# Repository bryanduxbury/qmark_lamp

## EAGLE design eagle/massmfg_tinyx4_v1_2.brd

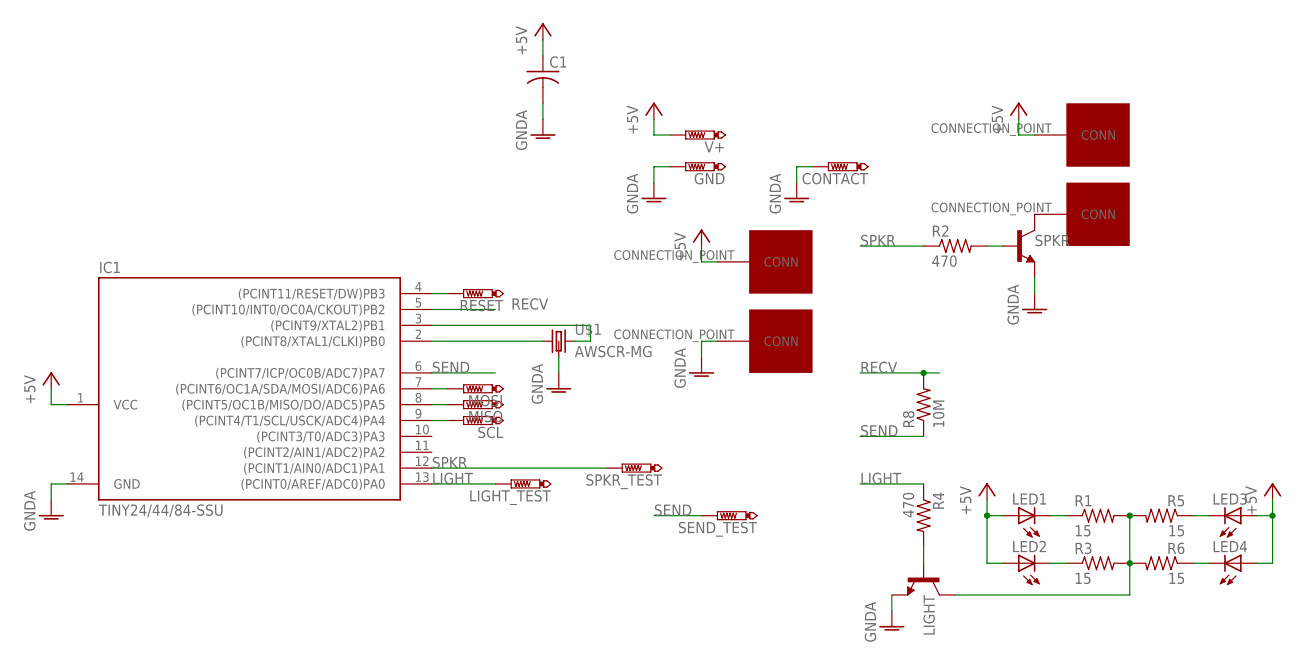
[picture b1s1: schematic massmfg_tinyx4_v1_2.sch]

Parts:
C1: C-USC0603; C0603
CONTACT: PTR1; P1-06
GND: PTR1; P1-06
IC1: TINY24/44/84-SSU; SOIC14
LED1, LED2, LED3, LED4: LEDOPTEK-DURIS5; OPTEK-DURIS5
LIGHT: SOT23-BEC
LIGHT_TEST: PTR1; P1-06
MISO: PTR1; P1-06
MOSI: PTR1; P1-06
R1, R3, R5, R6: 15; M1206
R2, R4: 470; R0805
R8: 10M; M1206
RESET: PTR1; P1-06
SCL: PTR1; P1-06
SEND_TEST: PTR1; P1-06
SPEAKER_PLUS: CONNECTION_POINT; 10X3_CONNECTION_POINT
SPKR: SOT23-BEC
SPKR_MINUS: CONNECTION_POINT; 10X3_CONNECTION_POINT
SPKR_TEST: PTR1; P1-06
U$1: AWSCR-MG
U$3, U$5: CONNECTION_POINT; 10X3_CONNECTION_POINT
V+: PTR1; P1-06

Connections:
+5V: C1.1, IC1.1 (VCC), LED1.ANODE (A), LED2.ANODE (A), LED3.ANODE (A), LED4.ANODE (A), SPEAKER_PLUS.CONNECTION_POINT, U$3.CONNECTION_POINT, V+.TP
GNDA: C1.2, CONTACT.TP, GND.TP, IC1.14 (GND), LIGHT.E, SPKR.E, U$1.GND (3), U$5.CONNECTION_POINT
LIGHT: IC1.13 ((PCINT0/AREF/ADC0)PA0), LIGHT_TEST.TP, R4.1
unnamed: LIGHT.B, R4.2
unnamed: IC1.2 ((PCINT8/XTAL1/CLKI)PB0), U$1.IN (1)
unnamed: LED2.CATHODE (C), R3.1
unnamed: IC1.3 ((PCINT9/XTAL2)PB1), U$1.OUT (2)
unnamed: LED1.CATHODE (C), R1.1
unnamed: R2.2, SPKR.B
unnamed: LED3.CATHODE (C), R5.1
unnamed: LED4.CATHODE (C), R6.1
unnamed: SPKR.C, SPKR_MINUS.CONNECTION_POINT
unnamed: IC1.4 ((PCINT11/RESET/DW)PB3), RESET.TP
unnamed: IC1.7 ((PCINT6/OC1A/SDA/MOSI/ADC6)PA6), MOSI.TP
unnamed: IC1.8 ((PCINT5/OC1B/MISO/DO/ADC5)PA5), MISO.TP
unnamed: IC1.9 ((PCINT4/T1/SCL/USCK/ADC4)PA4), SCL.TP
unnamed: LIGHT.C, R1.2, R3.2, R5.2, R6.2
RECV: IC1.5 ((PCINT10/INT0/OC0A/CKOUT)PB2), R8.2
SEND: IC1.6 ((PCINT7/ICP/OC0B/ADC7)PA7), R8.1, SEND_TEST.TP
SPKR: IC1.12 ((PCINT1/AIN0/ADC1)PA1), R2.1, SPKR_TEST.TP

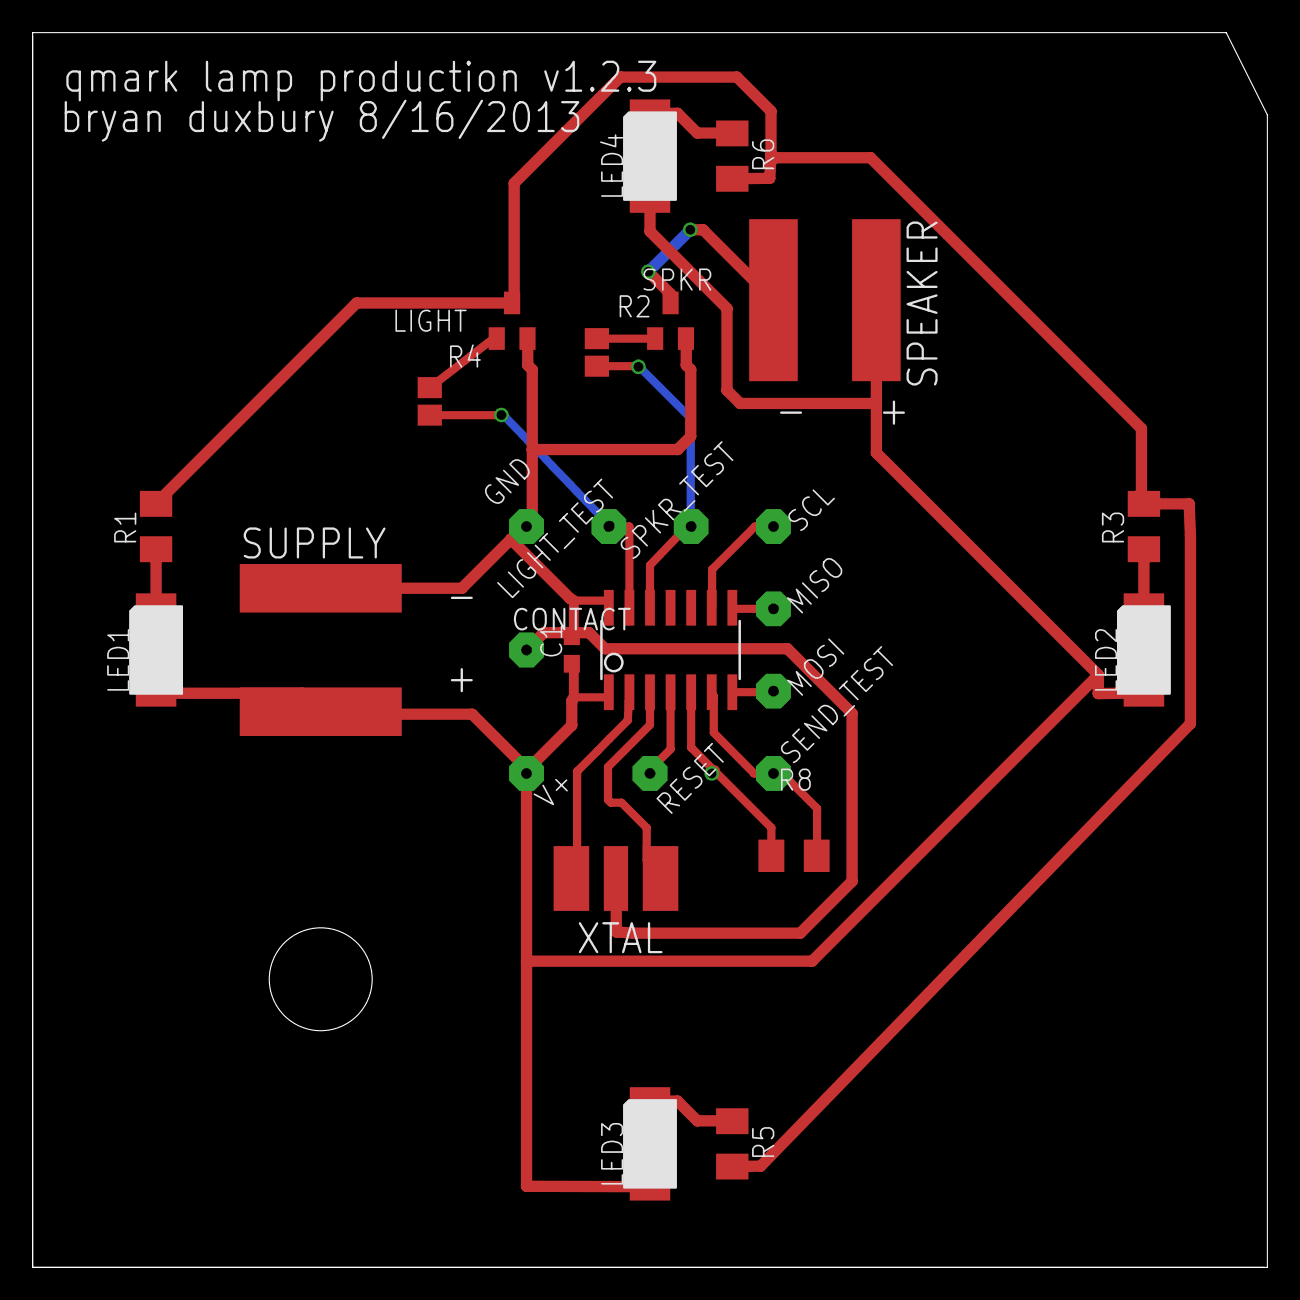
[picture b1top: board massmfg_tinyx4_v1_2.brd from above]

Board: 2 copper layers, 76.2 x 76.2 mm, 30 parts (0 on the bottom side), 20 nets.

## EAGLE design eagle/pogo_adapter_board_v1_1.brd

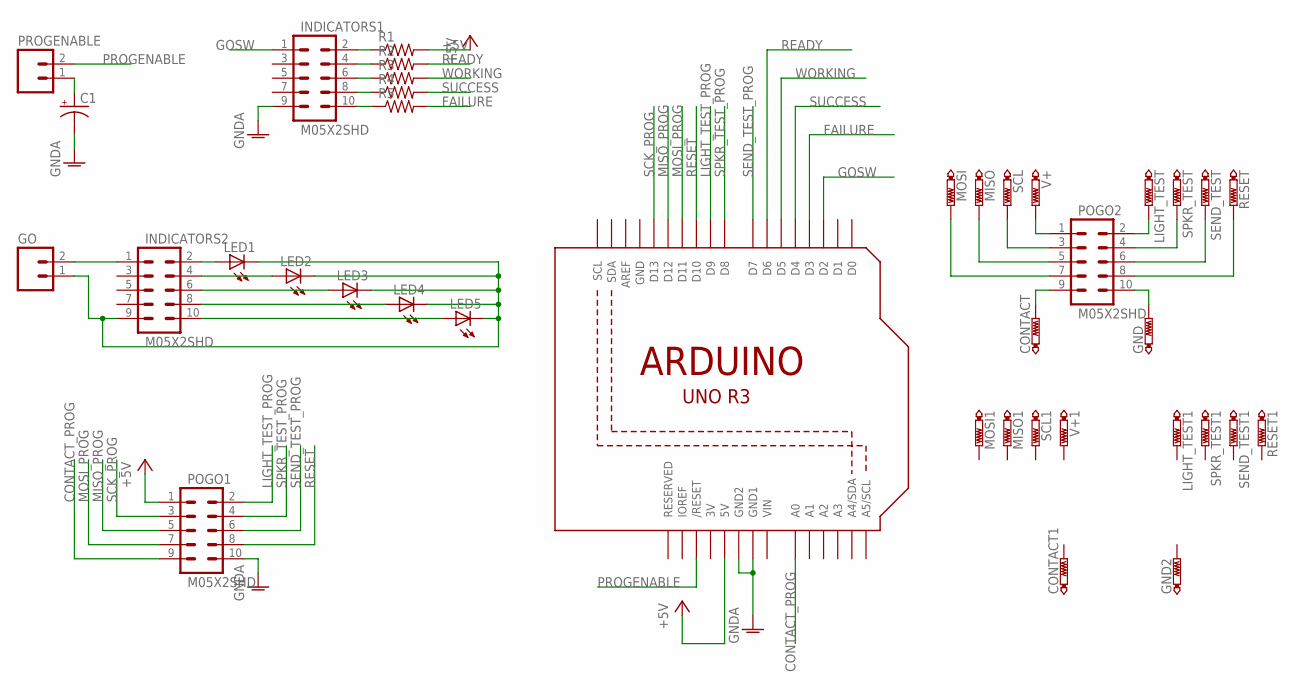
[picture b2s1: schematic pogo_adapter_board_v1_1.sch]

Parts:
C1: CAP_POLPTH2; CPOL-RADIAL-10UF-25V
CONTACT, CONTACT1: PTR1PAD1-13; P1-13
GND, GND2: PTR1PAD1-13; P1-13
GO: M02-JST-2-PTH-NO_SILK; JST-2-PTH-NS
INDICATORS1, INDICATORS2: M05X2SHD; 2X5-SHROUDED
LED1, LED2, LED3, LED4, LED5: LED10MM
LIGHT_TEST, LIGHT_TEST1: PTR1PAD1-13; P1-13
MISO, MISO1: PTR1PAD1-13; P1-13
MOSI, MOSI1: PTR1PAD1-13; P1-13
POGO1, POGO2: M05X2SHD; 2X5-SHROUDED
PROGENABLE: M02-JST-2-PTH-NO_SILK; JST-2-PTH-NS
R1, R2, R3, R4, R5: R-US_0204/7; 0204/7
RESET, RESET1: PTR1PAD1-13; P1-13
SCL, SCL1: PTR1PAD1-13; P1-13
SEND_TEST, SEND_TEST1: PTR1PAD1-13; P1-13
SPKR_TEST, SPKR_TEST1: PTR1PAD1-13; P1-13
U1: ARDUINOR3; ARDUINOR3-MINSHIELD
V+, V+1: PTR1PAD1-13; P1-13

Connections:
3V: U1.3V
+5V: POGO1.1, R1.2, U1.5V
CONTACT_PROG: POGO1.9, U1.A0
FAILURE: R5.2, U1.D3
GND: U1.GND
GNDA: C1.2 (-), INDICATORS1.9, POGO1.10, U1.GND1, U1.GND2
GOSW: INDICATORS1.1, U1.D2
LIGHT_TEST_PROG: POGO1.2, U1.D9
MISO_PROG: POGO1.5, U1.D12
MOSI_PROG: POGO1.7, U1.D11
unnamed: LIGHT_TEST.TP, POGO2.2
unnamed: POGO2.4, SPKR_TEST.TP
unnamed: POGO2.6, SEND_TEST.TP
unnamed: POGO2.8, RESET.TP
unnamed: GND.TP, POGO2.10
unnamed: GO.2, INDICATORS2.1
unnamed: CONTACT.TP, POGO2.9
unnamed: POGO2.3, SCL.TP
unnamed: MISO.TP, POGO2.5
unnamed: MOSI.TP, POGO2.7
unnamed: POGO2.1, V+.TP
unnamed: C1.1 (+), PROGENABLE.1
unnamed: INDICATORS2.2, LED1.A
unnamed: INDICATORS2.4, LED2.A
unnamed: INDICATORS2.6, LED3.A
unnamed: INDICATORS2.8, LED4.A
unnamed: INDICATORS2.10, LED5.A
unnamed: INDICATORS1.2, R1.1
unnamed: INDICATORS1.4, R2.1
unnamed: INDICATORS1.6, R3.1
unnamed: INDICATORS1.8, R4.1
unnamed: INDICATORS1.10, R5.1
unnamed: GO.1, INDICATORS2.9, LED1.K (C), LED2.K (C), LED3.K (C), LED4.K (C), LED5.K (C)
PROGENABLE: PROGENABLE.2, U1.RESET (/RESET)
READY: R2.2, U1.D6
RESET: POGO1.8, U1.D10
SCK_PROG: POGO1.3, U1.D13
SEND_TEST_PROG: POGO1.6, U1.D7
SPKR_TEST_PROG: POGO1.4, U1.D8
SUCCESS: R4.2, U1.D4
VIN: U1.VIN
WORKING: R3.2, U1.D5

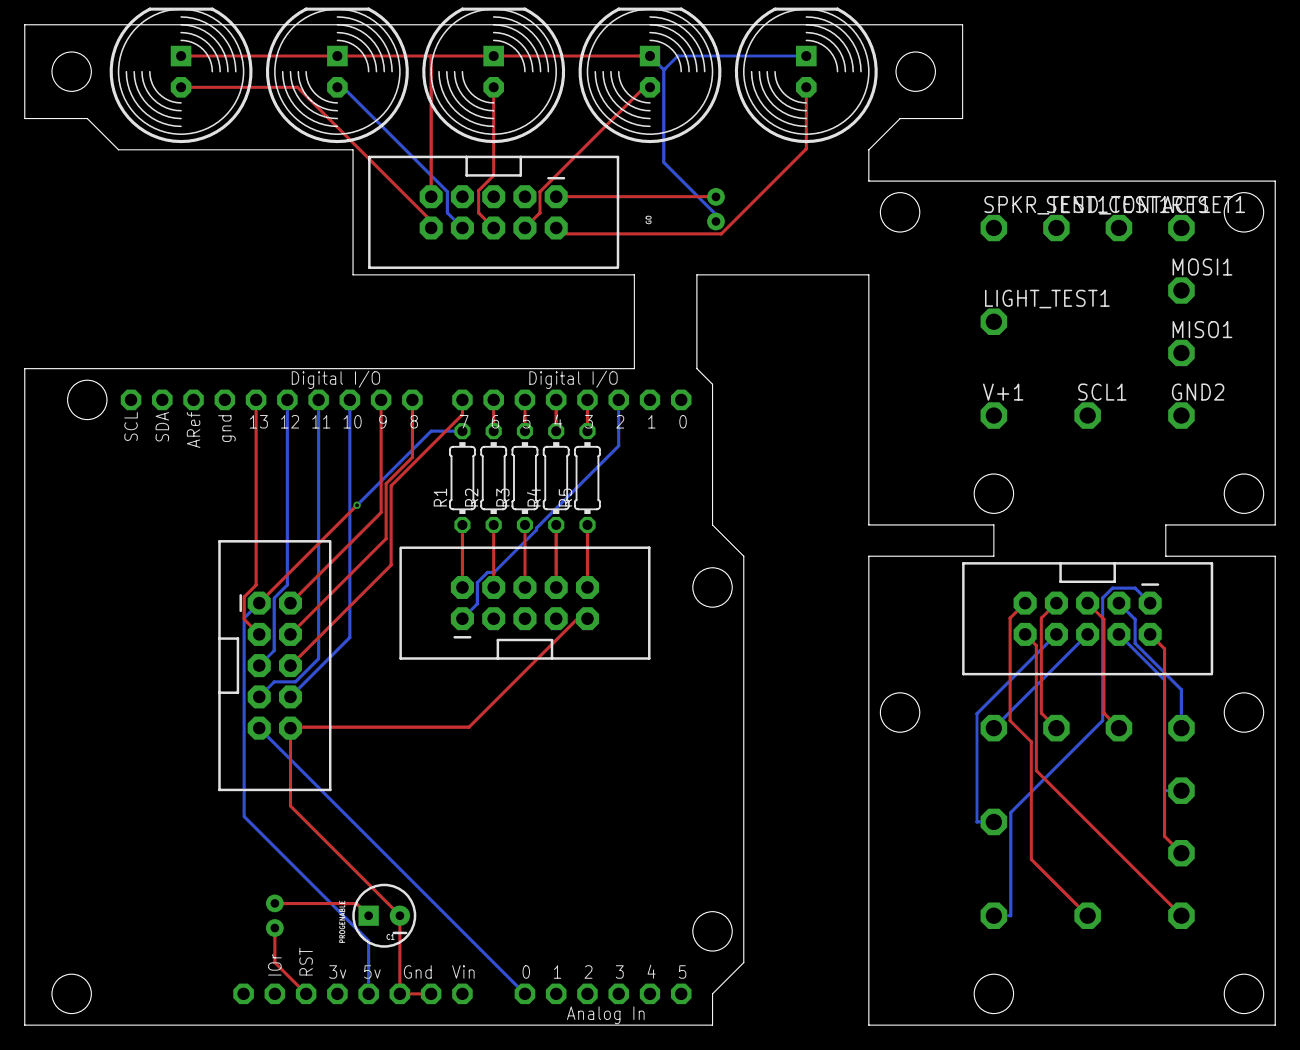
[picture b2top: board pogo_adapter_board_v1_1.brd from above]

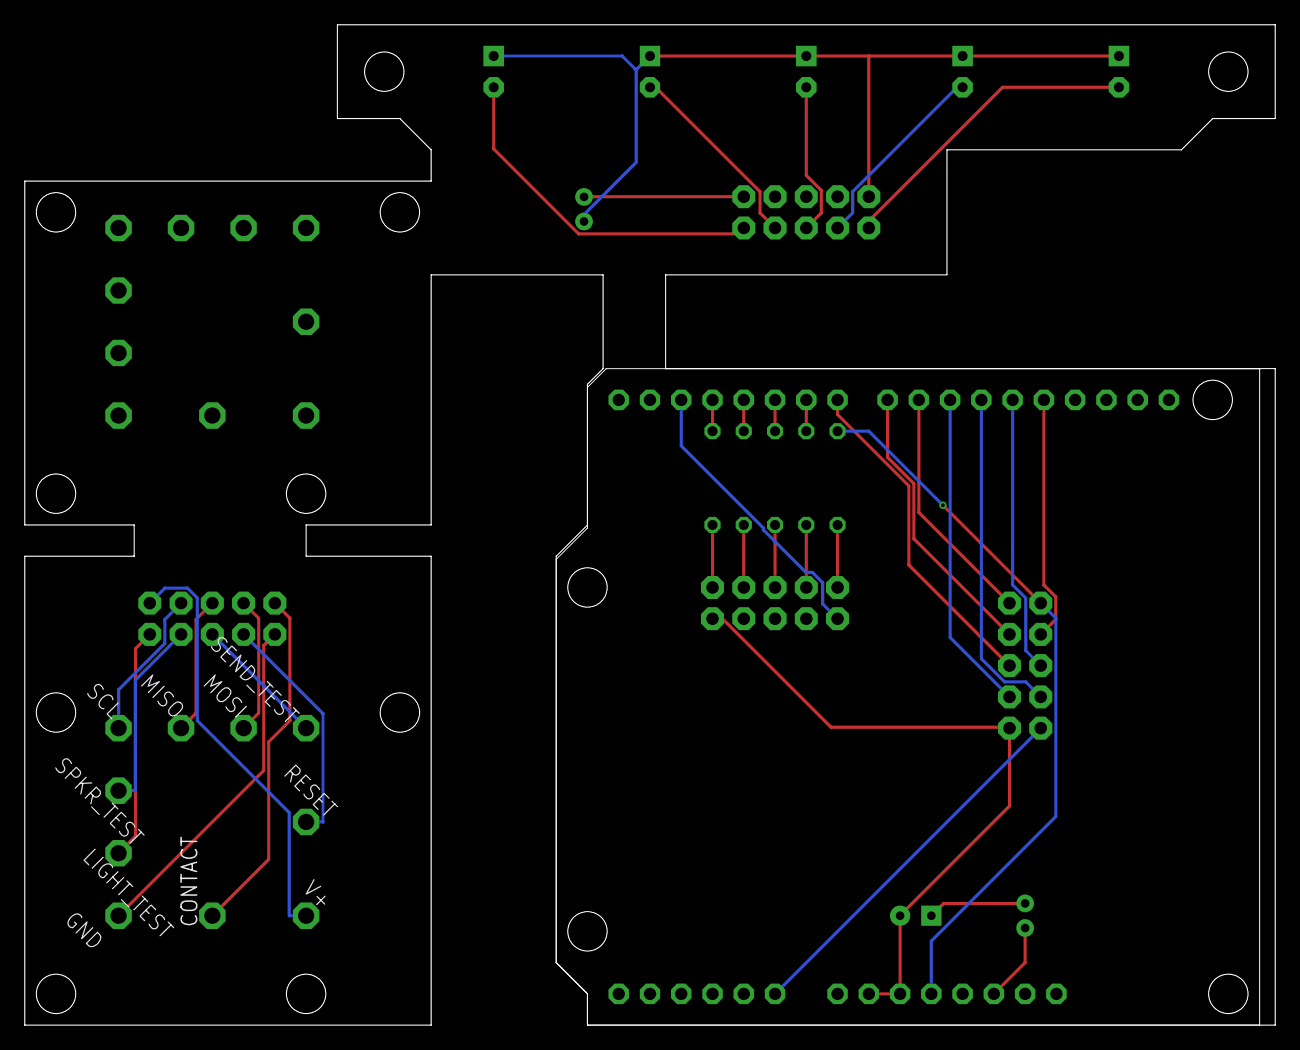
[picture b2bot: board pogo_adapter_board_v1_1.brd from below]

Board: 2 copper layers, 101.6 x 81.3 mm, 38 parts (10 on the bottom side), 39 nets.

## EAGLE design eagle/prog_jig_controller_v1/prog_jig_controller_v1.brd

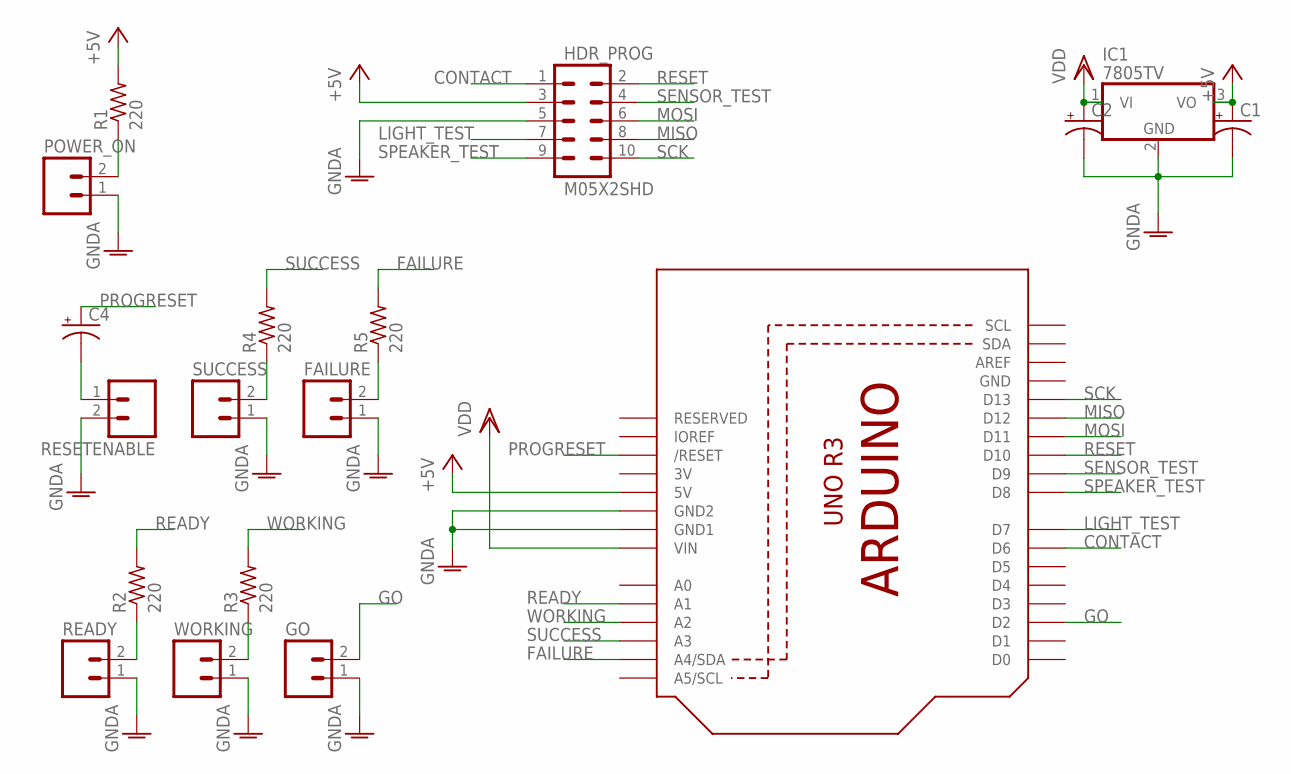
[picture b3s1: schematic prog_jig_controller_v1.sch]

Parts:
C1, C2, C4: CAP_POLPTH2; CPOL-RADIAL-10UF-25V
FAILURE: M02JST-PTH-2; JST-2-PTH
GO: M02JST-PTH-2; JST-2-PTH
HDR_PROG: M05X2SHD; 2X5-SHROUDED
IC1: 7805TV; TO220V
POWER_ON: M02JST-PTH-2; JST-2-PTH
R1, R2, R3, R4, R5: 220; 0204/7
READY: M02JST-PTH-2; JST-2-PTH
RESETENABLE: M02JST-PTH-2; JST-2-PTH
SUCCESS: M02JST-PTH-2; JST-2-PTH
U1: ARDUINOR3-DIMENSION; ARDUINOR3
WORKING: M02JST-PTH-2; JST-2-PTH

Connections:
3V: U1.3V
+5V: C1.1 (+), HDR_PROG.3, IC1.3 (VO), R1.2, U1.5V
CONTACT: HDR_PROG.1, U1.D6
FAILURE: R5.2, U1.A4 (A4/SDA)
GND: U1.GND
GNDA: C1.2 (-), C2.2 (-), FAILURE.1, GO.1, HDR_PROG.5, IC1.2 (GND), POWER_ON.1, READY.1, RESETENABLE.2, SUCCESS.1, U1.GND1, U1.GND2, WORKING.1
GO: GO.2, U1.D2
LIGHT_TEST: HDR_PROG.7, U1.D7
MISO: HDR_PROG.8, U1.D12
MOSI: HDR_PROG.6, U1.D11
unnamed: C4.2 (-), RESETENABLE.1
unnamed: POWER_ON.2, R1.1
unnamed: R4.1, SUCCESS.2
unnamed: R3.1, WORKING.2
unnamed: R2.1, READY.2
unnamed: FAILURE.2, R5.1
PROGRESET: C4.1 (+), U1.RESET (/RESET)
READY: R2.2, U1.A1
RESET: HDR_PROG.2, U1.D10
SCK: HDR_PROG.10, U1.D13
SENSOR_TEST: HDR_PROG.4, U1.D9
SPEAKER_TEST: HDR_PROG.9, U1.D8
SUCCESS: R4.2, U1.A3
VDD: C2.1 (+), IC1.1 (VI), U1.VIN
WORKING: R3.2, U1.A2

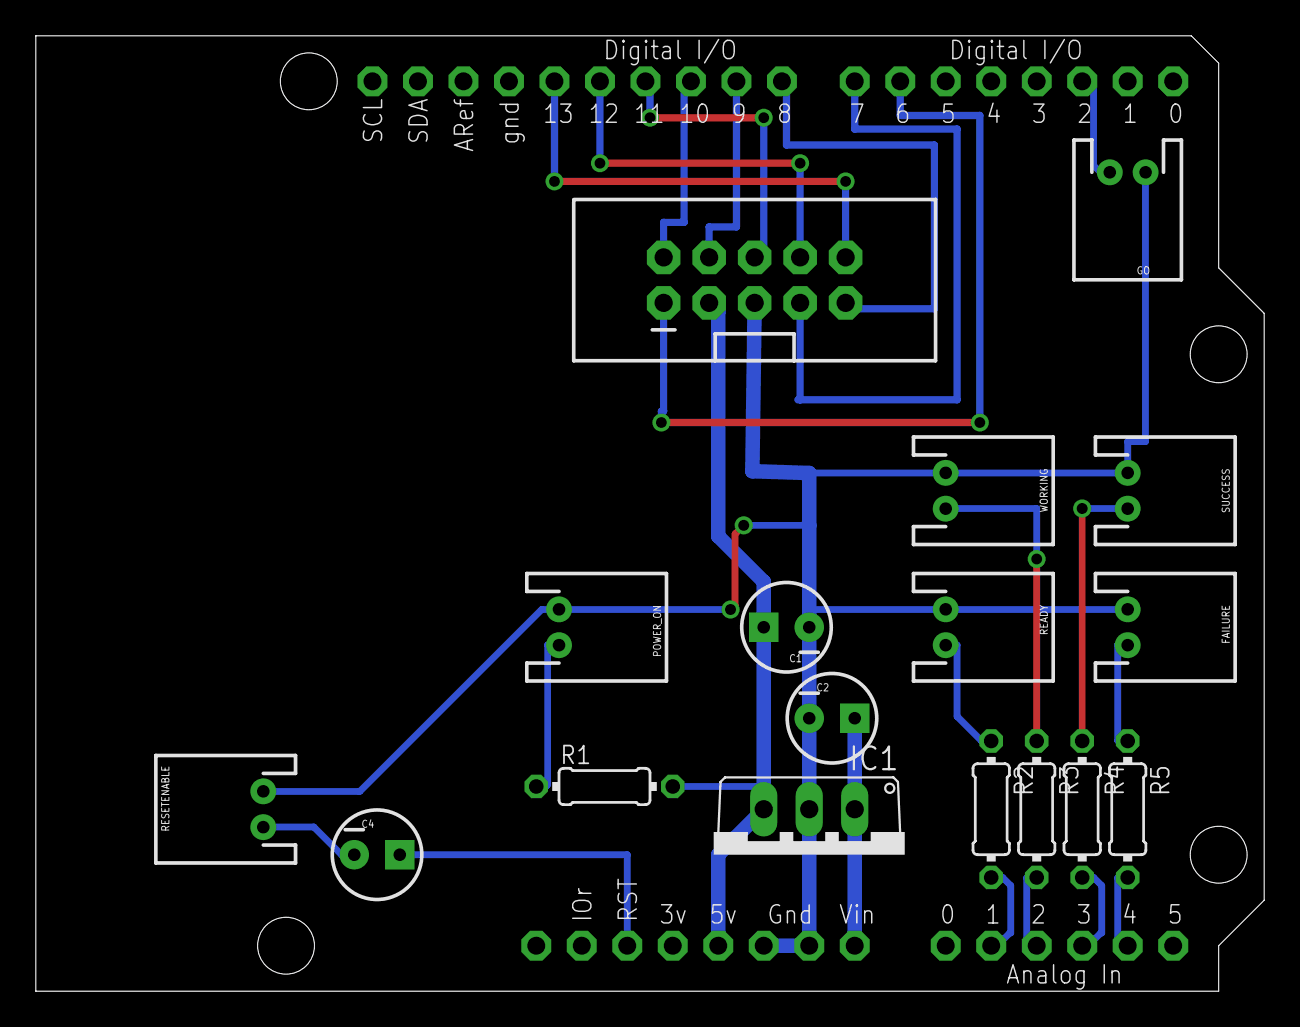
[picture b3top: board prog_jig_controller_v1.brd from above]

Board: 2 copper layers, 68.6 x 53.3 mm, 18 parts (0 on the bottom side), 23 nets.

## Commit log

2011-12-19 initial import of existing files
2011-12-20 shrink down to a 6 inch box; export dxfs of the pieces
2011-12-21 changes to firmware to make it run on an attiny
2012-01-02 tuned the firmware to work with 4" electrode and 10M resistor
2012-01-03 added circuit board stencil for lasercutting
2012-01-04 convert stroke to path
2012-01-04 add board file
2012-01-05 upload cleaned up versions of circuit board
2012-01-06 -oh, i guess i forgot to commit some of the schematic -add a new board design
2012-01-06 updates to board and circuit, single version of newer board layout
2012-01-07 clean up the firmware
2012-01-07 adjust dimension of box to 5.75 inches
2012-01-07 don't play the coin sound when you get a 1-up
2012-01-10 commit new smd circuit design, some small changes to firmware, first batch of photos
2012-01-11 re export the black 5.75 panel
2012-01-11 new exports, slight mods to circuits
2012-01-11 remove some older exports
2012-01-13 -reduce touch threshold in firmware -add bounding box to circuit board -re-export eps's with bounding box added
2012-01-19 small updates to firmware
2012-01-19 add drawings dir and some kerf adjusted exports
2012-01-19 modifications to scad file to work well with laser kerf
2012-01-19 move exported drawings into drawings/
2012-01-19 make eagle subdir, move stuff in
2012-01-19 push the sawtooth out to the edge slightly
2012-01-21 remove the tiny flanges issue
2012-01-21 re-export
2012-02-02 adjust the size of the laser beam based on measurements; re-exported dxfs based on new kerf adjustments
2012-02-02 add photos we took for kit purposes
2012-02-02 draft of board to be sent to seeed
2012-02-02 make that black panel more prolific
2012-02-12 add smd circuit and board, along with library of parts needed
2012-02-12 changes to the circuit design sent away to seeed
2012-02-12 the arbitrary value gods have spoken - 150 is the touch threshold
2012-02-12 modification to make the black panel fit as many pieces as possible into 1 sq ft
2012-02-12 all the photos i've been uploading for the kit instructables
2012-02-12 exported and cleaned eps of smd board
2012-02-12 rename export.eps to smd_circuit.eps
2012-02-12 cam job for exporting to eps... going to need some work
2012-02-14 add 2.5 inch drawings
2012-02-18 update cnc file with a solder paste stencil segment
2012-02-18 solder paste stencil file
2012-02-18 forgot to save some changes
2012-02-23 commit some outstanding stuff
2012-02-25 remove a photo
2012-02-28 silk stencil, hooray
2012-02-28 eps version
2012-03-01 add design for 30x30mm smd board
2012-03-01 panel of 96 30x30mm boards
2012-03-05 exported gerbers
2012-03-06 2x5 panel of shrunken smd circuits
2012-03-06 board layout for 20x20mm smd
2012-03-06 add zip file containing the tiny85 core we've been using
2012-03-06 outstanding changes
2012-03-06 dividing lines
2012-03-09 some kerf variations
2012-03-20 add paste stencil
2012-03-20 2x2 panelized design
2012-04-03 add a bunch of photos/movies
2012-04-26 v2 of the kit board: better silkscreen, single point for the sensor
2012-04-26 a bunch of photos
2012-04-26 75mm integrated sensor board designs
2012-04-29 updated brd files for latest pcb order
2012-05-11 updated paste stencil for new boards with wider spacing
2012-05-11 new draft of the 75mm board
2012-05-11 updated gitignore
2012-05-11 draft of files for the 18" version
2012-07-21 move some old stuff into old/ dir
2012-07-21 trash some old eps's
2012-08-26 new version of firmware that works with the attiny84
2012-09-05 new board for mass manufacture
2012-09-05 draft of programming jig for mass mfg board
2012-09-05 misc changes
2012-09-05 some new smd parts
2013-03-22 board design for the pogopin programming board
2013-03-22 changes to smd_parts library
2013-03-22 uncommitted changes to scad
2013-03-22 uncommitted changes to schematics
2013-03-22 redefined parameters for tinyx4 boards
2013-04-11 boards for the programming fixture
2013-04-13 wowza, lots of progress on the programming fixture
2013-04-13 -updated lamp board -programming jig super-board kit
2013-04-13 added speaker grille to top of box
2013-04-13 added some necessary tab slots, designed and positioned the led strip
2013-04-13 almost done
2013-04-14 looks like it's done
2013-04-17 mockup of a flatpack pipe-styled stand
2013-04-17 redesign the pogo board not to hang silk screen off the edge of the board, since that makes seeed unhappy
2013-04-17 adjust the touch threshold for the new boards
2013-04-17 fixed a few bugs detected during the first cut-out
2013-04-17 add DS_Store to gitignore
2013-04-17 some slight mods to tinyx4 board
2013-04-18 final adjustments to programming fixture
2013-05-13 other small updates to programming fixture
2013-05-13 slight improvements to the lamp board
2013-07-23 new version of production board, now with a bypass cap to protect the uC
2013-07-23 update the silkscreen
2013-07-23 make sure to initialize the speaker pin at startup
2013-07-23 updated programming fixture to make the board frame fit nicely
2013-07-23 exploratory sinewave firmware
2013-08-08 latest updates to board based on EEs comments
2013-08-08 wrote up instructions for a handful of programmer related stuff
2013-08-08 some minor polishing
2013-08-12 add the star sequence
2013-09-22 board and firmware changes

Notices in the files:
parts and their libraries:
SparkFun: Licensing: CC v3.0 Share-Alike You are welcome to use this library for commercial purposes.
